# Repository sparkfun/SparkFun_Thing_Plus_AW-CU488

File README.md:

SparkFun AzureWave Thing Plus (AW-CU488)
========================================

[*SparkFun AzureWave Thing Plus (AW-CU488) (DEV-19957)*](https://www.sparkfun.com/products/19957)

The SparkFun AzureWave Thing Plus is a Feather form-factor development board equipped with the AW-CU488. The module features the Realtek RTL8721DM integrated single-chip low-power dual-band (2.4GHz and 5GHz) wireless LAN <!--and Bluetooth&reg; Low Energy (V5.0) --> communication controller. It also consists of a dual processor core: Real-M300 CPU (ARMv8-M, Cortex-M33) and Real-M200 CPU (ARMv8-M, Cortex-M23). Connect the SparkFun AzureWave Thing Plus to the cloud to grab current weather conditions in your area, post sensor data to a server, control the lights in your next home automation project, or even calculate the Fast Fourier Transform (FFT) of an input audio signal!

Why the name? We lovingly call it the “Thing” because it's perfect for your Internet of Things project. The Thing does everything from turning on an LED to posting data with your chosen platform and can be programmed just like any microcontroller. You can even program the Thing through the Arduino IDE by installing the [Realtek Arduino core](https://github.com/ambiot/ambd_arduino). 

The board includes a USB-C connector for programming and power. Two buttons for reset and boot are also populated on the board. For those that need to go remote with their application, the board includes a 2-pin JST connector and the MCP73831 single cell, LiPo charge IC (set to a default rate of 500mA). Voltage is regulated down for the AW-CU488 with the XC6222 3.3V/700mA voltage regulator. Three status LEDs are available for power, charging, and status. Due to the size of the module, the board is slightly longer than the standard Thing Plus footprint. With the added length, we were able to break out a few more PTHs on the edge of the board for a total of 30 GPIO pins (30 Interrupts, seven Analog, 11 PWM, two UARTs, two SPI, and a single I<sup>2</sup>C). The board also includes a built-in audio CODEC with two channel analog inputs and outputs at various sample rates (8/12/16/24/32/48/.../176.4 kHz). On the back of the board are five jumpers for the LiPo charge rate, LED, auto boot circuit, and USB shielding. Finally, one Qwiic connector is populated on the board to easily add Qwiic-enabled I<sup>2</sup>C devices to your projects! 

Repository Contents
-------------------

* **/Documentation** - Datasheets, additional product information
* **/Hardware** - Eagle design files (.brd, .sch)
  * **/Production** - Production panel files (.brd)

Documentation
--------------

* **[Board Definitions](https://github.com/ambiot/ambd_arduino)** - Arduino board support files for the SparkFun AzureWave Thing Plus (AW-CU488)
* **[Hookup Guide](https://learn.sparkfun.com/tutorials/2518)** - Basic hookup guide

Product Versions
----------------

* [DEV-19957](https://www.sparkfun.com/products/19957) - Initial release

Version History
---------------
* v1.0 - Initial release

License Information
-------------------

This product is _**open source**_! 

Please review the LICENSE.md file for license information. 

If you have any questions or concerns on licensing, please contact technical support on our [SparkFun forums](https://forum.sparkfun.com/viewforum.php?f=152).

Distributed as-is; no warranty is given.

- Your friends at SparkFun.

_<COLLABORATION CREDIT>_

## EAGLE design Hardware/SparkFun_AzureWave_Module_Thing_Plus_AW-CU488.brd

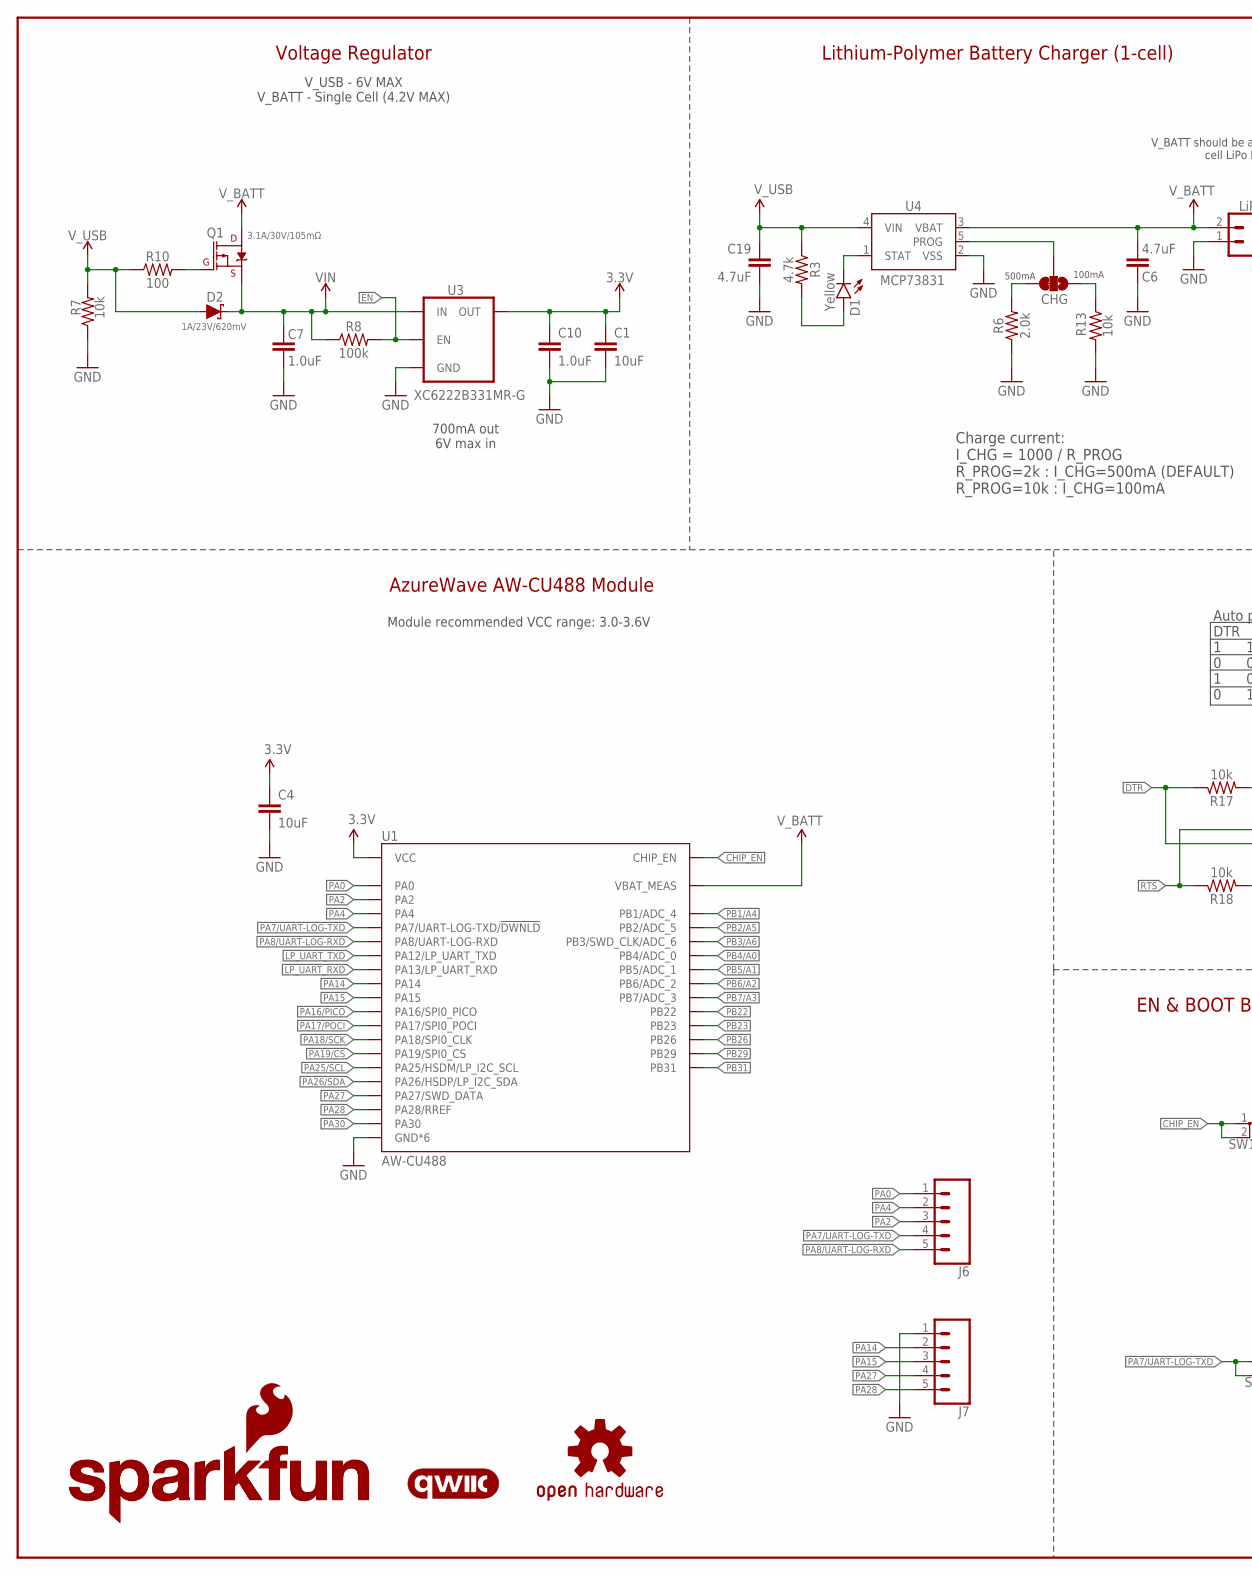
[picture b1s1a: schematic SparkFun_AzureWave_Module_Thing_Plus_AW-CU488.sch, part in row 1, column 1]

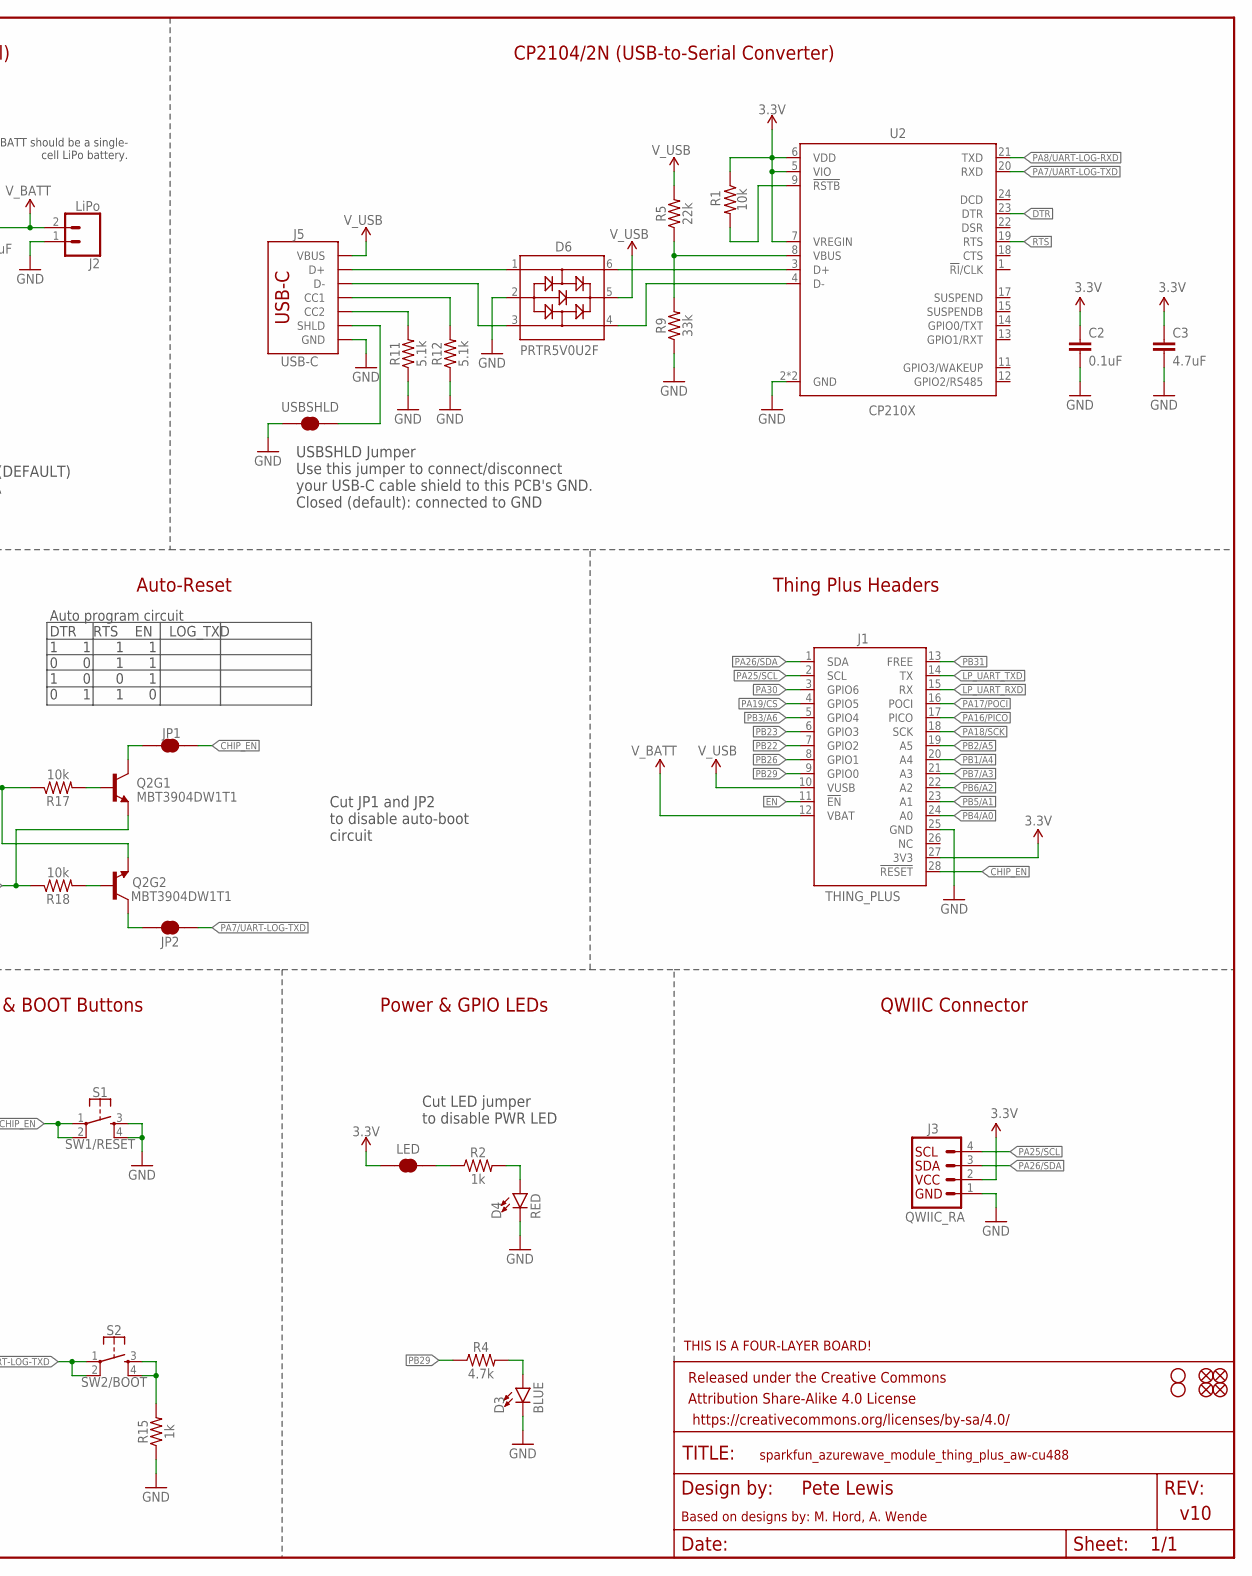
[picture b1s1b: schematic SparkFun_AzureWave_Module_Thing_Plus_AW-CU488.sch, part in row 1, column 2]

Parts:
C1: 10uF; 0402-TIGHT
C2: 0.1uF; 0402-TIGHT
C3, C6, C19: 4.7uF; 0402-TIGHT
C4: 10uF; 0603
C7, C10: 1.0uF; 0402-TIGHT
CHG: JUMPER-SMT_3_1-NC_TRACE_SILK; SMT-JUMPER_3_1-NC_TRACE_SILK
D1: Yellow; LED-0603
D2: 1A/23V/620mV; SOD-323
D3: BLUE; LED-0603
D4: RED; LED-0603
D6: PRTR5V0U2F; SOT886
FD1, FD2, FD3, FD4: FIDUCIALUFIDUCIAL; FIDUCIAL-MICRO
FRAME1: FRAME-LEDGER; CREATIVE_COMMONS
H1, H2: STAND-OFF
J1: THING_PLUS
J2: LiPo; JST-2-SMD
J3: QWIIC_RA; JST04_1MM_RA
J5: USB-C; USB-C-16P-4LAYER-ISOLATED
J6, J7: CONN_05NO_SILK; 1X05_NO_SILK
JP1, JP2: JUMPER-SMT_2_NC_TRACE_SILK; SMT-JUMPER_2_NC_TRACE_SILK
LED: JUMPER-SMT_2_NC_TRACE_SILK; SMT-JUMPER_2_NC_TRACE_SILK
LOGO1: SFE_LOGO_NAME.1_INCH; SFE_LOGO_NAME_.1
LOGO2: OSHW-LOGOMINI; OSHW-LOGO-MINI
LOGO3: SFE_LOGO_NAME_FLAME.1_INCH; SFE_LOGO_NAME_FLAME_.1
LOGO4: FOUR_LAYER_WARNING
LOGO6: QWIIC_LOGO_4MM; QWIIC_4MM
Q1: 3.1A/30V/105mΩ; SOT23-3
Q2: MBT3904DW1T1; SC70-6
R1, R7, R13, R17, R18: 10k; 0402-TIGHT
R2, R15: 1k; 0402-TIGHT
R3, R4: 4.7k; 0402-TIGHT
R5: 22k; 0402-TIGHT
R6: 2.0k; 0603
R8: 100k; 0402-TIGHT
R9: 33k; 0402-TIGHT
R10: 100; 0402-TIGHT
R11, R12: 5.1k; 0402-TIGHT
S1: SW1/RESET; TACTILE_SWITCH_SMD_4.6X2.8MM
S2: SW2/BOOT; TACTILE_SWITCH_SMD_4.6X2.8MM
U1: AW-CU488; LGA150_AW-CU488
U2: CP210X; QFN24
U3: XC6222B331MR-G; SOT23-5
U4: MCP73831; SOT23-5
USBSHLD: JUMPER-SMT_2_NC_TRACE_SILK; SMT-JUMPER_2_NC_TRACE_SILK

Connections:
3.3V: C1.1, C2.1, C3.1, C4.1, C10.1, J1.27 (3V3), J3.2, LED.1, R1.1, U1.F1 (VCC), U2.5 (VIO), U2.6 (VDD), U2.7 (VREGIN), U3.5 (OUT)
CC1: J5.A5 (CC1), R12.2
CC2: J5.B5 (CC2), R11.2
CHG: D1.C, U4.1 (STAT)
CHIP_EN: J1.28 (!RESET), JP1.2, S1.1, S1.2, U1.K11 (CHIP_EN)
DTR: Q2.1 (E), R17.1, U2.23 (DTR)
EN: J1.11 (!EN), R8.2, U3.3 (EN)
GND: C1.2, C2.2, C3.2, C4.2, C6.2, C7.2, C10.2, C19.2, D3.C, D4.C, D6.2, J1.25 (GND), J2.1 (2), J3.1, J5.GND, J5.GND2 (GND), J7.1, R6.1, R7.1, R9.1, R11.1, R12.1, R13.2, R15.1, S1.3, S1.4, U1.A1 (GND*6), U1.A2 (GND*6), U1.A14 (GND*6), U1.A15 (GND*6), U1.B14 (GND*6), U1.B15 (GND*6), U1.C3 (GND*6), U1.C4 (GND*6), U1.C5 (GND*6), U1.C6 (GND*6), U1.C7 (GND*6), U1.C8 (GND*6), U1.C9 (GND*6), U1.C10 (GND*6), U1.C11 (GND*6), U1.C12 (GND*6), U1.C13 (GND*6), U1.C14 (GND*6), U1.C15 (GND*6), U1.D3 (GND*6), U1.D4 (GND*6), U1.D5 (GND*6), U1.D6 (GND*6), U1.D7 (GND*6), U1.D8 (GND*6), U1.D9 (GND*6), U1.D10 (GND*6), U1.D11 (GND*6), U1.D12 (GND*6), U1.D13 (GND*6), U1.D14 (GND*6), U1.D15 (GND*6), U1.E1 (GND*6), U1.E2 (GND*6), U1.E3 (GND*6), U1.E4 (GND*6), U1.E5 (GND*6), U1.E6 (GND*6), U1.E7 (GND*6), U1.E8 (GND*6), U1.E9 (GND*6), U1.E10 (GND*6), U1.E11 (GND*6), U1.E12 (GND*6), U1.E13 (GND*6), U1.E14 (GND*6), U1.E15 (GND*6), U1.F2 (GND*6), U1.F3 (GND*6), U1.F4 (GND*6), U1.F5 (GND*6), U1.F6 (GND*6), U1.F7 (GND*6), U1.F8 (GND*6), U1.F9 (GND*6), U1.F10 (GND*6), U1.F11 (GND*6), U1.F12 (GND*6), U1.F13 (GND*6), U1.F14 (GND*6), U1.F15 (GND*6), U1.G1 (GND*6), U1.G2 (GND*6), U1.G3 (GND*6), U1.G4 (GND*6), U1.G5 (GND*6), U1.G6 (GND*6), U1.G7 (GND*6), U1.G8 (GND*6), U1.G9 (GND*6), U1.G10 (GND*6), U1.G11 (GND*6), U1.G12 (GND*6), U1.G13 (GND*6), U1.G14 (GND*6), U1.G15 (GND*6), U1.H3 (GND*6), U1.H4 (GND*6), U1.H5 (GND*6), U1.H6 (GND*6), U1.H7 (GND*6), U1.H8 (GND*6), U1.H9 (GND*6), U1.H10 (GND*6), U1.H11 (GND*6), U1.H12 (GND*6), U1.H13 (GND*6), U1.H14 (GND*6), U1.H15 (GND*6), U1.J14 (GND*6), U1.J15 (GND*6), U1.K3 (GND*6), U1.K4 (GND*6), U1.K14 (GND*6), U1.K15 (GND*6), U2.2 (GND), U2.PAD (GND), U3.2 (GND), U4.2 (VSS), USBSHLD.1
LP_UART_RXD: J1.15 (RX), U1.B13 (PA13/LP_UART_RXD)
LP_UART_TXD: J1.14 (TX), U1.A13 (PA12/LP_UART_TXD)
unnamed: R1.2, U2.9 (!RSTB)
unnamed: D3.A, R4.2
unnamed: Q2.5 (B), R17.2
unnamed: R5.1, R9.2, U2.8 (VBUS)
unnamed: Q2.2 (B), R18.2
unnamed: JP1.1, Q2.3 (C)
unnamed: Q1.1 (G), R10.2
unnamed: R15.2, S2.3, S2.4
unnamed: CHG.2, U4.5 (PROG)
unnamed: JP2.1, Q2.6 (C)
unnamed: CHG.1, R13.1
unnamed: LED.2, R2.1
unnamed: CHG.3, R6.2
unnamed: D4.A, R2.2
unnamed: D6.6, U2.3 (D+)
unnamed: D6.1, J5.A6 (D+), J5.B6 (D+)
unnamed: D1.A, R3.2
unnamed: D6.4, U2.4 (D-)
unnamed: D6.3, J5.A7 (D-), J5.B7 (D-)
PA0: J6.1, U1.K8 (PA0)
PA2: J6.3, U1.K10 (PA2)
PA4: J6.2, U1.K9 (PA4)
PA7/UART-LOG-TXD: J6.4, JP2.2, S2.1, S2.2, U1.K12 (PA7/UART-LOG-TXD/!DWNLD!), U2.20 (RXD)
PA8/UART-LOG-RXD: J6.5, U1.K13 (PA8/UART-LOG-RXD), U2.21 (TXD)
PA14: J7.2, U1.A12 (PA14)
PA15: J7.3, U1.B12 (PA15)
PA16/PICO: J1.17 (PICO), U1.A11 (PA16/SPI0_PICO)
PA17/POCI: J1.16 (POCI), U1.B11 (PA17/SPI0_POCI)
PA18/SCK: J1.18 (SCK), U1.A10 (PA18/SPI0_CLK)
PA19/CS: J1.4 (GPIO5), U1.B10 (PA19/SPI0_CS)
PA25/SCL: J1.2 (SCL), J3.4, U1.A5 (PA25/HSDM/LP_I2C_SCL)
PA26/SDA: J1.1 (SDA), J3.3, U1.A6 (PA26/HSDP/LP_I2C_SDA)
PA27: J7.4, U1.A9 (PA27/SWD_DATA)
PA28: J7.5, U1.A7 (PA28/RREF)
PA30: J1.3 (GPIO6), U1.A8 (PA30)
PB1/A4: J1.20 (A4), U1.A3 (PB1/ADC_4)
PB2/A5: J1.19 (A5), U1.A4 (PB2/ADC_5)
PB3/A6: J1.5 (GPIO4), U1.B1 (PB3/SWD_CLK/ADC_6)
PB4/A0: J1.24 (A0), U1.B2 (PB4/ADC_0)
PB5/A1: J1.23 (A1), U1.C1 (PB5/ADC_1)
PB6/A2: J1.22 (A2), U1.C2 (PB6/ADC_2)
PB7/A3: J1.21 (A3), U1.D1 (PB7/ADC_3)
PB22: J1.7 (GPIO2), U1.K1 (PB22)
PB23: J1.6 (GPIO3), U1.K2 (PB23)
PB26: J1.8 (GPIO1), U1.K5 (PB26)
PB29: J1.9 (GPIO0), R4.1, U1.K6 (PB29)
PB31: J1.13 (FREE), U1.K7 (PB31)
RTS: Q2.4 (E), R18.1, U2.19 (RTS)
USB_SHLD: J5.SHLD1 (SHLD), J5.SHLD2 (SHLD), J5.SHLD3 (SHLD), J5.SHLD4 (SHLD), J5.SHLD5 (SHLD), J5.SHLD6 (SHLD), J5.SHLD7 (SHLD), J5.SHLD8 (SHLD), USBSHLD.2
VIN: C7.1, D2.C, Q1.2 (S), R8.1, U3.1 (IN)
V_BATT: C6.1, J1.12 (VBAT), J2.2 (1), Q1.3 (D), U1.D2 (VBAT_MEAS), U4.3 (VBAT)
V_USB: C19.1, D2.A, D6.5, J1.10 (VUSB), J5.VBUS1 (VBUS), J5.VBUS2 (VBUS), R3.1, R5.2, R7.2, R10.1, U4.4 (VIN)

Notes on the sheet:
CP2104/2N (USB-to-Serial Converter)
V_BATT should be a single- cell LiPo battery.
Charge current: I_CHG = 1000 / R_PROG R_PROG=2k : I_CHG=500mA (DEFAULT) R_PROG=10k : I_CHG=100mA
Voltage Regulator
Lithium-Polymer Battery Charger (1-cell)
700mA out 6V max in
AzureWave AW-CU488 Module
Thing Plus Headers
v10
QWIIC Connector
Pete Lewis
Power & GPIO LEDs
Based on designs by: M. Hord, A. Wende
V_USB - 6V MAX V_BATT - Single Cell (4.2V MAX)
100mA
500mA
Module recommended VCC range: 3.0-3.6V
EN & BOOT Buttons
Auto program circuit DTR RTS EN LOG_TXD 1 1 1 1 0 0 1 1 1 0 0 1 0 1 1 0
Auto-Reset
USBSHLD Jumper Use this jumper to connect/disconnect your USB-C cable shield to this PCB's GND. Closed (default): connected to GND
Cut JP1 and JP2 to disable auto-boot circuit
Cut LED jumper to disable PWR LED

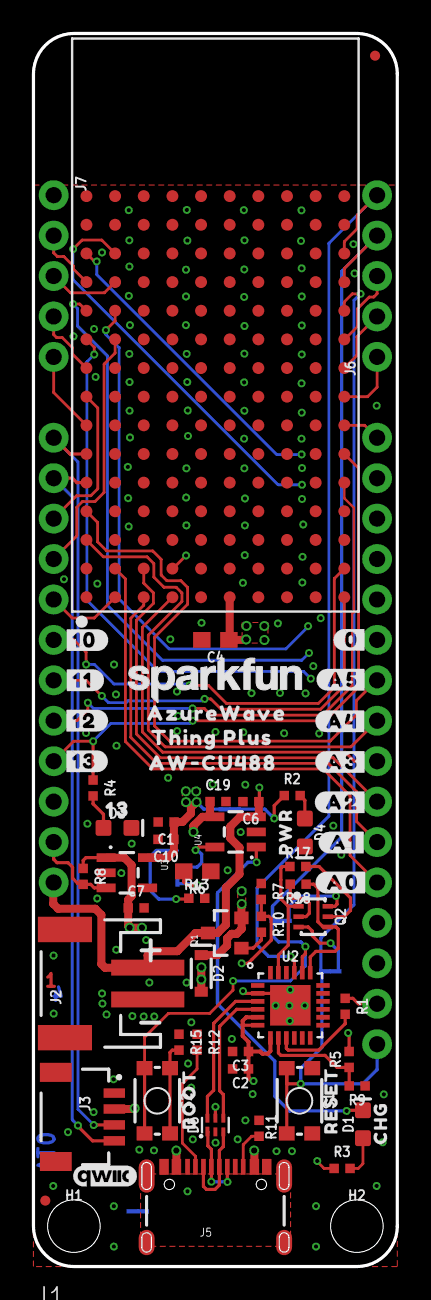
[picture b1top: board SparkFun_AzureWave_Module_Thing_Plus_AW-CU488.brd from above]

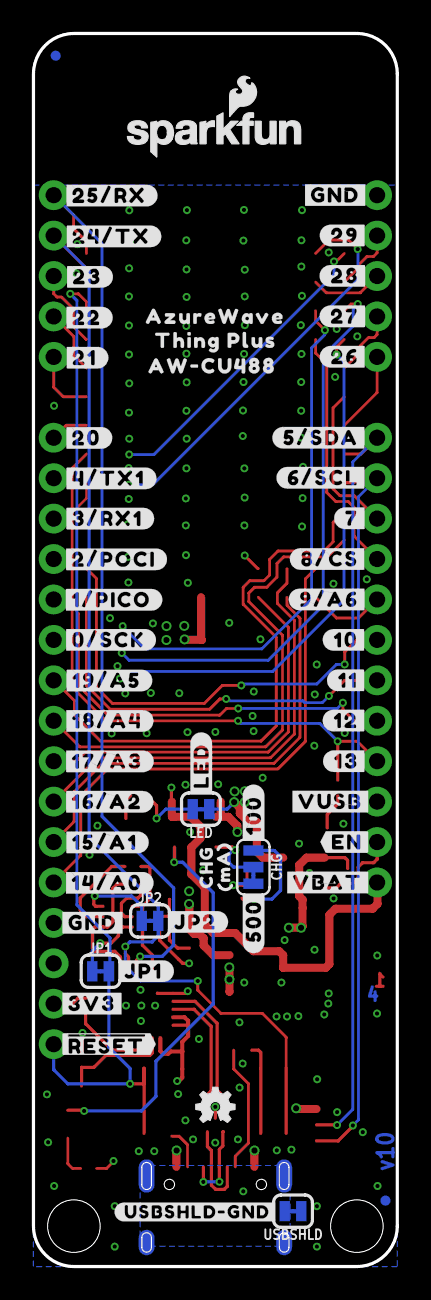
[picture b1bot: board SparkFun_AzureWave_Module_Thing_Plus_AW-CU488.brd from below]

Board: 4 copper layers, 22.9 x 77.5 mm, 128 parts (57 on the bottom side), 62 nets.

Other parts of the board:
U$1: #10#30
U$2: BOOT0
U$3, U$78: CHG0
U$4: #500#0
U$5: #11#30
U$6, U$8: AZUREWAVE0
U$7: 1330
U$9, U$27: AW#CU488_0
U$10, U$62: THING_PLUS_0
U$11: MA0
U$12: #12#30
U$14: #13#30
U$15: #JP1#1
U$16: #0#1
U$18: #A0#30
U$19: #JP2#4
U$20: #USBSHLD#GND#3
U$23: PWR0
U$29: #LED#0
U$32, U$86: #GND#0
U$41: #VUSB#0
U$42: #VBAT#0
U$43: #EN#0
U$45: #3V3#0
U$46: ##RESET##0
U$48: #4#TX1#14
U$49: #3#RX1#14
U$50: #2#POCI#14
U$53: #A1#6
U$54: #A2#6
U$55: #A3#6
U$56: #A4#6
U$57: #A5#6
U$59: ORDERING_INSTRUCTIONS
U$60: #100#0
U$64: #1#PICO#14
U$67: #13#14
U$68: #12#14
U$69: #11#14
U$70: #10#14
U$71: #9#A6#14
U$72: #8#CS#14
U$73: #7#14
U$74: #6#SCL#14
U$75: #5#SDA#14
U$76: #0#SCK#14
U$77: #14#A0#15
U$79: RESET0
U$80: #15#A1#15
U$81: #16#A2#16
U$82: #17#A3#17
U$83: #18#A4#18
U$84: #19#A5#19
U$85: #20#20
U$87: #21#21
U$88: #22#22
U$89: #23#23
U$90: #24#TX#24
U$91: #25#RX#25
U$92: #26#26
U$93: #27#27
U$94: #28#28
U$95: #29#29

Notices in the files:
parts and their libraries:
SparkFun-Resistors: Licensing: Creative Commons ShareAlike 4.0 International - https://creativecommons.org/licenses/by-sa/4.0
SparkFun-Aesthetics: Released under the Creative Commons Attribution Share-Alike 4.0 License
SparkFun-Aesthetics: https://creativecommons.org/licenses/by-sa/4.0
